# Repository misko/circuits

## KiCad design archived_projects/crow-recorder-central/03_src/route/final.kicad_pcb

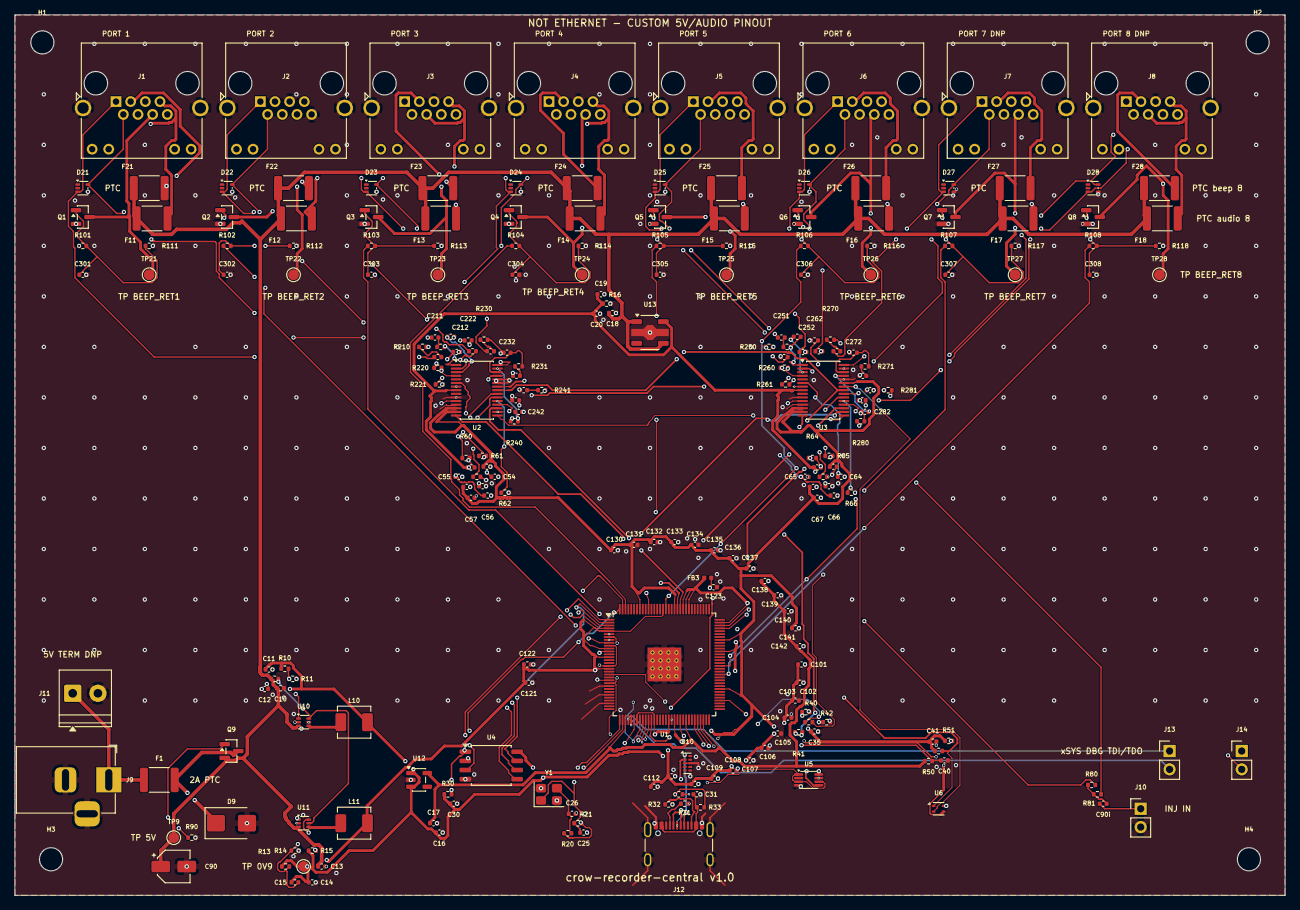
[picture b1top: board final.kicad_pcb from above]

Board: 6 copper layers, 176.0 x 122.0 mm, 238 parts (0 on the bottom side), 151 nets.

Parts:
C10, C13, C18: 4u7 VIN; C_0402_1005Metric
C11, C136, C137: 10u 3V3; C_0402_1005Metric
C12: 100p FF; C_0402_1005Metric
C14: 22u 0V9; C_0402_1005Metric
C15: 560p FF; C_0402_1005Metric
C16: 1u VIN; C_0402_1005Metric
C17: 1u 1V8; C_0402_1005Metric
C19: 10u 3V3A; C_0402_1005Metric
C20: 100n 3V3A; C_0402_1005Metric
C25: 18p CL1; C_0402_1005Metric
C26: 18p CL2; C_0402_1005Metric
C30: 100n flash; C_0402_1005Metric
C31: 1u VBUS; C_0402_1005Metric
C35: 100n buf; C_0402_1005Metric
C40: 10n RST; C_0402_1005Metric
C41: 100n SHT; C_0402_1005Metric
C50: 4u7 AVDD_A; C_0402_1005Metric
C51: 100n AVDD_A; C_0402_1005Metric
C52: 4u7 DVDD_A; C_0402_1005Metric
C53: 100n DVDD_A; C_0402_1005Metric
C54: 2u2 VREF_A; C_0402_1005Metric
C55: 2u2 LDO_A; C_0402_1005Metric
C56: 100n LDO_A; C_0402_1005Metric
C57: 100n IOV_A; C_0402_1005Metric
C60: 4u7 AVDD_B; C_0402_1005Metric
C61: 100n AVDD_B; C_0402_1005Metric
C62: 4u7 DVDD_B; C_0402_1005Metric
C63: 100n DVDD_B; C_0402_1005Metric
C64: 2u2 VREF_B; C_0402_1005Metric
C65: 2u2 LDO_B; C_0402_1005Metric
C66: 100n LDO_B; C_0402_1005Metric
C67: 100n IOV_B; C_0402_1005Metric
C90: 100u 5V bulk; CP_Elec_4x5.4
C90i: 1u inj; C_0402_1005Metric
C101, C102, C103, C104, C105, C106, C107, C108, C109, C110, C111, C112: 100n VDD; C_0402_1005Metric
C121, C122: 10u VDD; C_0402_1005Metric
C123: 1u PLL; C_0402_1005Metric
C130, C131, C132, C133, C134, C135: 100n 3V3; C_0402_1005Metric
C138, C139: 100n 1V8; C_0402_1005Metric
C140: 10u 1V8; C_0402_1005Metric
C141: 100n USB33; C_0402_1005Metric
C142: 100n USB18; C_0402_1005Metric
C210: 1u cpl P1; C_0402_1005Metric
C211: 1u cpl N1; C_0402_1005Metric
C212: 1n diff 1; C_0402_1005Metric
C220: 1u cpl P2; C_0402_1005Metric
C221: 1u cpl N2; C_0402_1005Metric
C222: 1n diff 2; C_0402_1005Metric
C230: 1u cpl P3; C_0402_1005Metric
C231: 1u cpl N3; C_0402_1005Metric
C232: 1n diff 3; C_0402_1005Metric
C240: 1u cpl P4; C_0402_1005Metric
C241: 1u cpl N4; C_0402_1005Metric
C242: 1n diff 4; C_0402_1005Metric
C250: 1u cpl P5; C_0402_1005Metric
C251: 1u cpl N5; C_0402_1005Metric
C252: 1n diff 5; C_0402_1005Metric
C260: 1u cpl P6; C_0402_1005Metric
C261: 1u cpl N6; C_0402_1005Metric
C262: 1n diff 6; C_0402_1005Metric
C270: 1u cpl P7; C_0402_1005Metric
C271: 1u cpl N7; C_0402_1005Metric
C272: 1n diff 7; C_0402_1005Metric
C280: 1u cpl P8; C_0402_1005Metric
C281: 1u cpl N8; C_0402_1005Metric
C282: 1n diff 8; C_0402_1005Metric
C301: 4n7 gate 1; C_0402_1005Metric
C302: 4n7 gate 2; C_0402_1005Metric
C303: 4n7 gate 3; C_0402_1005Metric
C304: 4n7 gate 4; C_0402_1005Metric
C305: 4n7 gate 5; C_0402_1005Metric
C306: 4n7 gate 6; C_0402_1005Metric
C307: 4n7 gate 7; C_0402_1005Metric
C308: 4n7 gate 8; C_0402_1005Metric
D9: SMBJ5.0A TVS; D_SMB
D10: TPD4EUSB30; USON-10_2.5x1.0mm_P0.5mm
D21: TPD2E2U06 p1; SOT-553
D22: TPD2E2U06 p2; SOT-553
D23: TPD2E2U06 p3; SOT-553
D24: TPD2E2U06 p4; SOT-553
D25: TPD2E2U06 p5; SOT-553
D26: TPD2E2U06 p6; SOT-553
D27: TPD2E2U06 p7; SOT-553
D28: TPD2E2U06 p8; SOT-553
F1: 2A PTC; Fuse_1812_4532Metric
F11: PTC audio 1; Fuse_1812_4532Metric
F12: PTC audio 2; Fuse_1812_4532Metric
F13: PTC audio 3; Fuse_1812_4532Metric
F14: PTC audio 4; Fuse_1812_4532Metric
F15: PTC audio 5; Fuse_1812_4532Metric
F16: PTC audio 6; Fuse_1812_4532Metric
F17: PTC audio 7; Fuse_1812_4532Metric
F18: PTC audio 8; Fuse_1812_4532Metric
F21: PTC beep 1; Fuse_1812_4532Metric
F22: PTC beep 2; Fuse_1812_4532Metric
F23: PTC beep 3; Fuse_1812_4532Metric
F24: PTC beep 4; Fuse_1812_4532Metric
F25: PTC beep 5; Fuse_1812_4532Metric
F26: PTC beep 6; Fuse_1812_4532Metric
F27: PTC beep 7; Fuse_1812_4532Metric
F28: PTC beep 8; Fuse_1812_4532Metric
FB3: 600R PLL; L_0402_1005Metric
H1, H2, H3, H4: MountingHole_3.2mm_M3
J1, J2, J3, J4, J5, J6: RJHSE-5384; RJ45_Amphenol_RJHSE538X
J7, J8: RJHSE-5384 DNP; RJ45_Amphenol_RJHSE538X
J9: DC-005 5V IN; BarrelJack_Horizontal
J10: INJ IN; PinHeader_1x02_P2.54mm_Vertical
J11: 5V TERM DNP; TerminalBlock_Phoenix_PT-1,5-2-3.5-H_1x02_P3.50mm_Horizontal
J12: USB4105-GF-A; USB_C_Receptacle_GCT_USB4105-xx-A_16P_TopMnt_Horizontal
J13: xSYS DBG TDI/TDO; PinHeader_1x02_P2.54mm_Vertical
J14: xSYS DBG TMS/TCK; PinHeader_1x02_P2.54mm_Vertical
L10: 1u0 3V3; L_Sunlord_MWSA0402S
L11: 1u0 0V9; L_Sunlord_MWSA0402S
Q1: AO3400A beep 1; SOT-23
Q2: AO3400A beep 2; SOT-23
Q3: AO3400A beep 3; SOT-23
Q4: AO3400A beep 4; SOT-23
Q5: AO3400A beep 5; SOT-23
Q6: AO3400A beep 6; SOT-23
Q7: AO3400A beep 7; SOT-23
Q8: AO3400A beep 8; SOT-23
Q9: AO3401A revFET; SOT-23
R10: 68k FB1 hi; R_0402_1005Metric
R11: 15k FB1 lo; R_0402_1005Metric
R12: 10k PG1 pu; R_0402_1005Metric
R13: 10k FB2 hi; R_0402_1005Metric
R14: 20k FB2 lo; R_0402_1005Metric
R15: 10k PG2 pu; R_0402_1005Metric
R16: 4k7 bleed; R_0402_1005Metric
R20: 680R Rd; R_0402_1005Metric
R21: 1M Rf; R_0402_1005Metric
R30: 10k CS pu; R_0402_1005Metric
R31: 5k1 CC1 Rd; R_0402_1005Metric
R32: 5k1 CC2 Rd; R_0402_1005Metric
R33: 220k VBUS; R_0402_1005Metric
R34: 330k VBUS; R_0402_1005Metric
R40: 33R MCLK_A; R_0402_1005Metric
R41: 33R MCLK_B; R_0402_1005Metric
R42: 33R BCLK; R_0402_1005Metric
R43: 33R LRCK; R_0402_1005Metric
R50: 10k RST pu; R_0402_1005Metric
R51: 4k7 SCL pu; R_0402_1005Metric
R52: 4k7 SDA pu; R_0402_1005Metric
R60: 100k GP0_A; R_0402_1005Metric
R61: 100k GP1_A; R_0402_1005Metric
R62: 100k GP2_A; R_0402_1005Metric
R63: 100k GP3_A; R_0402_1005Metric
R64: 100k GP0_B; R_0402_1005Metric
R65: 100k GP1_B; R_0402_1005Metric
R66: 100k GP2_B; R_0402_1005Metric
R67: 100k GP3_B; R_0402_1005Metric
R80: 1k inj ch4; R_0402_1005Metric
R81: 1k inj ch8; R_0402_1005Metric
R90: 100k FET gate; R_0402_1005Metric
R101: 1k gate 1; R_0402_1005Metric
R102: 1k gate 2; R_0402_1005Metric
R103: 1k gate 3; R_0402_1005Metric
R104: 1k gate 4; R_0402_1005Metric
R105: 1k gate 5; R_0402_1005Metric
R106: 1k gate 6; R_0402_1005Metric
R107: 1k gate 7; R_0402_1005Metric
R108: 1k gate 8; R_0402_1005Metric
R111: 100k pd 1; R_0402_1005Metric
R112: 100k pd 2; R_0402_1005Metric
R113: 100k pd 3; R_0402_1005Metric
R114: 100k pd 4; R_0402_1005Metric
R115: 100k pd 5; R_0402_1005Metric
R116: 100k pd 6; R_0402_1005Metric
R117: 100k pd 7; R_0402_1005Metric
R118: 100k pd 8; R_0402_1005Metric
R210: 49R9 P1; R_0402_1005Metric
R211: 49R9 N1; R_0402_1005Metric
R220: 49R9 P2; R_0402_1005Metric
R221: 49R9 N2; R_0402_1005Metric
R230: 49R9 P3; R_0402_1005Metric
R231: 49R9 N3; R_0402_1005Metric
R240: 49R9 P4; R_0402_1005Metric
R241: 49R9 N4; R_0402_1005Metric
R250: 49R9 P5; R_0402_1005Metric
R251: 49R9 N5; R_0402_1005Metric
R260: 49R9 P6; R_0402_1005Metric
R261: 49R9 N6; R_0402_1005Metric
R270: 49R9 P7; R_0402_1005Metric
R271: 49R9 N7; R_0402_1005Metric
R280: 49R9 P8; R_0402_1005Metric
R281: 49R9 N8; R_0402_1005Metric
TP9: TP 5V; TestPoint_Pad_D1.5mm
TP11: TP 0V9; TestPoint_Pad_D1.5mm
TP21: TP BEEP_RET1; TestPoint_Pad_D1.5mm
TP22: TP BEEP_RET2; TestPoint_Pad_D1.5mm
TP23: TP BEEP_RET3; TestPoint_Pad_D1.5mm
TP24: TP BEEP_RET4; TestPoint_Pad_D1.5mm
TP25: TP BEEP_RET5; TestPoint_Pad_D1.5mm
TP26: TP BEEP_RET6; TestPoint_Pad_D1.5mm
TP27: TP BEEP_RET7; TestPoint_Pad_D1.5mm
TP28: TP BEEP_RET8; TestPoint_Pad_D1.5mm
U1: XU316-1024-TQ128-I24; TQFP-128_14x14mm_P0.4mm_EP4.7mm
U2, U3: PCM1865DBTR; TSSOP-30_4.4x7.8mm_P0.5mm
U4: W25Q16JVSSIQ; SOIC-8_5.3x5.3mm_P1.27mm
U5: NC7NZ34 MCLK buf; VSSOP-8_2.3x2mm_P0.5mm
U6: SHT40-AD1B (0x44); Sensirion_DFN-4_1.5x1.5mm_P0.8mm_SHT4x_NoCentralPad
U10: AP61102 3V3; SOT-563
U11: AP61102 0V9; SOT-563
U12: TCR2LF18 1V8; SOT-23-5
U13: XC6227 3V3A; SOT-89-5
Y1: FA-238 24MHz; Crystal_SMD_3225-4Pin_3.2x2.5mm

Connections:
0V9: C14.1, C15.1, C101.1, C102.1, C103.1, C104.1, C105.1, C106.1, C107.1, C108.1, C109.1, C110.1, C111.1, C112.1, C121.1, C122.1, FB3.1, L11.2, R13.1, TP11.1, U1.5, U1.11, U1.14, U1.18, U1.39, U1.45, U1.50, U1.54, U1.68, U1.85, U1.95, U1.104, U1.105, U1.106, U1.113
1V8: C17.1, C138.1, C139.1, C140.1, C142.1, R50.1, U1.35, U1.56, U1.62, U12.5
3V3: C11.1, C12.1, C16.1, C30.1, C35.1, C41.1, C52.1, C53.1, C57.1, C62.1, C63.1, C67.1, C130.1, C131.1, C132.1, C133.1, C134.1, C135.1, C136.1, C137.1, C141.1, L10.2, R10.1, R15.1, R30.1, R51.1, R52.1, U1.10, U1.17, U1.40, U1.43, U1.52, U1.61, U1.72, U1.89, U1.109, U1.121, U2.13, U2.14, U3.13, U3.14, U3.25, U4.8, U5.8, U6.3, U12.1, U12.3
3V3A: C19.1, C20.1, C50.1, C51.1, C60.1, C61.1, R16.1, U2.8, U3.8, U13.5
5V: C10.1, C13.1, C18.1, C90.1, F11.1, F12.1, F13.1, F14.1, F15.1, F16.1, F17.1, F18.1, F21.1, F22.1, F23.1, F24.1, F25.1, F26.1, F27.1, F28.1, Q9.2, R12.1, TP9.1, U10.3, U10.5, U11.3, U13.1, U13.4
5V_AUD1: F11.2, J1.4, J1.7
5V_AUD2: F12.2, J2.4, J2.7
5V_AUD3: F13.2, J3.4, J3.7
5V_AUD4: F14.2, J4.4, J4.7
5V_AUD5: F15.2, J5.4, J5.7
5V_AUD6: F16.2, J6.4, J6.7
5V_AUD7: F17.2, J7.4, J7.7
5V_AUD8: F18.2, J8.4, J8.7
5V_IN: F1.1, J9.1, J11.1
5V_P: D9.1, F1.2, Q9.3
AIN_N1: C211.2, R211.1
AIN_N2: C221.2, R221.1
AIN_N3: C231.2, R231.1
AIN_N4: C241.2, R241.1
AIN_N5: C251.2, R251.1
AIN_N6: C261.2, R261.1
AIN_N7: C271.2, R271.1
AIN_N8: C281.2, R281.1
AIN_P1: C210.2, R210.1
AIN_P2: C220.2, R220.1
AIN_P3: C230.2, R230.1
AIN_P4: C240.2, R80.2, R240.1
AIN_P5: C250.2, R250.1
AIN_P6: C260.2, R260.1
AIN_P7: C270.2, R270.1
AIN_P8: C280.2, R81.2, R280.1
AUD_N1: C211.1, D21.5, J1.2
AUD_N2: C221.1, D22.5, J2.2
AUD_N3: C231.1, D23.5, J3.2
AUD_N4: C241.1, D24.5, J4.2
AUD_N5: C251.1, D25.5, J5.2
AUD_N6: C261.1, D26.5, J6.2
AUD_N7: C271.1, D27.5, J7.2
AUD_N8: C281.1, D28.5, J8.2
AUD_P1: C210.1, D21.3, J1.1
AUD_P2: C220.1, D22.3, J2.1
AUD_P3: C230.1, D23.3, J3.1
AUD_P4: C240.1, D24.3, J4.1
AUD_P5: C250.1, D25.3, J5.1
AUD_P6: C260.1, D26.3, J6.1
AUD_P7: C270.1, D27.3, J7.1
AUD_P8: C280.1, D28.3, J8.1
BCLK: R42.2, U2.17, U3.17
BCLK_X: R42.1, U1.22
BEEP_5V1: F21.2, J1.3
BEEP_5V2: F22.2, J2.3
BEEP_5V3: F23.2, J3.3
BEEP_5V4: F24.2, J4.3
BEEP_5V5: F25.2, J5.3
BEEP_5V6: F26.2, J6.3
BEEP_5V7: F27.2, J7.3
BEEP_5V8: F28.2, J8.3
BEEP_G1: R101.1, U1.6
BEEP_G2: R102.1, U1.9
BEEP_G3: R103.1, U1.12
BEEP_G4: R104.1, U1.126
BEEP_G5: R105.1, U1.118
BEEP_G6: R106.1, U1.112
BEEP_G7: R107.1, U1.80
BEEP_G8: R108.1, U1.77
BEEP_RET1: J1.6, Q1.3, TP21.1
BEEP_RET2: J2.6, Q2.3, TP22.1
BEEP_RET3: J3.6, Q3.3, TP23.1
BEEP_RET4: J4.6, Q4.3, TP24.1
BEEP_RET5: J5.6, Q5.3, TP25.1
BEEP_RET6: J6.6, Q6.3, TP26.1
BEEP_RET7: J7.6, Q7.3, TP27.1
BEEP_RET8: J8.6, Q8.3, TP28.1
BG_1: C301.1, Q1.1, R101.2, R111.1
BG_2: C302.1, Q2.1, R102.2, R112.1
BG_3: C303.1, Q3.1, R103.2, R113.1
BG_4: C304.1, Q4.1, R104.2, R114.1
BG_5: C305.1, Q5.1, R105.2, R115.1
BG_6: C306.1, Q6.1, R106.2, R116.1
BG_7: C307.1, Q7.1, R107.2, R117.1
BG_8: C308.1, Q8.1, R108.2, R118.1
BK1_PG: R12.2, U10.6, U11.5
BK1_SW: L10.1, U10.4
BK2_PG: R15.2, U11.6
BK2_SW: L11.1, U11.4
CC1: J12.A5, R31.1
CC2: J12.B5, R32.1
DATA1: U1.107, U2.18
DATA2: U1.108, U3.18
FB1: C12.2, R10.2, R11.1, U10.1
FB2: C15.2, R13.2, R14.1, U11.1
GATE9: Q9.1, R90.1
GND: C10.2, C11.2, C13.2, C14.2, C16.2, C17.2, C18.2, C19.2, C20.2, C25.2, C26.2, C30.2, C31.2, C35.2, C40.2, C41.2, C50.2, C51.2, C52.2, C53.2, C54.2, C55.2, C56.2, C57.2, C60.2, C61.2, C62.2, C63.2, C64.2, C65.2, C66.2, C67.2, C90.2, C101.2, C102.2, C103.2, C104.2, C105.2, C106.2, C107.2, C108.2, C109.2, C110.2, C111.2, C112.2, C121.2, C122.2, C123.2, C130.2, C131.2, C132.2, C133.2, C134.2, C135.2, C136.2, C137.2, C138.2, C139.2, C140.2, C141.2, C142.2, C301.2, C302.2, C303.2, C304.2, C305.2, C306.2, C307.2, C308.2, D9.2, D10.3, D10.8, D21.4, D22.4, D23.4, D24.4, D25.4, D26.4, D27.4, D28.4, J1.5, J1.8, J1.SH, J2.5, J2.8, J2.SH, J3.5, J3.8, J3.SH, J4.5, J4.8, J4.SH, J5.5, J5.8, J5.SH, J6.5, J6.8, J6.SH, J7.5, J7.8, J7.SH, J8.5, J8.8, J8.SH, J9.2, J9.3, J10.2, J11.2, J12.A1, J12.A12, J12.B1, J12.B12, J12.SH, Q1.2, Q2.2, Q3.2, Q4.2, Q5.2, Q6.2, Q7.2, Q8.2, R11.2, R14.2, R16.2, R31.2, R32.2, R34.2, R60.2, R61.2, R62.2, R63.2, R64.2, R65.2, R66.2, R67.2, R90.2, R111.2, R112.2, R113.2, R114.2, R115.2, R116.2, R117.2, R118.2, U1.24, U1.27, U1.30, U1.42, U1.129, U2.7, U2.10, U2.12, U2.25, U2.26, U3.7, U3.10, U3.12, U3.26, U4.4, U5.4, U6.4, U10.2, U11.2, U12.2, U13.2, Y1.2, Y1.4
GP0_A: R60.1, U2.22
GP0_B: R64.1, U3.22
GP1_A: R61.1, U2.21
GP1_B: R65.1, U3.21
GP2_A: R62.1, U2.20
GP2_B: R66.1, U3.20
GP3_A: R63.1, U2.19
GP3_B: R67.1, U3.19
I2C_SCL: R51.2, U1.93, U2.24, U3.24, U6.2
I2C_SDA: R52.2, U1.94, U2.23, U3.23, U6.1
INJ: C90i.1, J10.1
INJ_C: C90i.2, R80.1, R81.1
LDO_A: C55.1, C56.1, U2.11
LDO_B: C65.1, C66.1, U3.11
LRCK: R43.2, U2.16, U3.16
LRCK_X: R43.1, U1.20
MCLK_A: R40.2, U2.15
MCLK_A0: R40.1, U5.7
MCLK_B: R41.2, U3.15
MCLK_B0: R41.1, U5.5
MCLK_SRC: U1.7, U1.23, U5.1, U5.3, U5.6
PLL_AVDD: C123.1, FB3.2, U1.41
QSPI_CLK: U1.4, U4.6
QSPI_CS: R30.2, U1.2, U4.1
QSPI_D0: U1.127, U4.5
QSPI_D1: U1.128, U4.2
QSPI_D2: U1.1, U4.3
QSPI_D3: U1.3, U4.7
RST_N: C40.1, R50.2, U1.38
TCK: J14.2, U1.51
TDI: J13.1, U1.36
TDO: J13.2, U1.37
TMS: J14.1, U1.44
USB_DM: D10.2, J12.A7, J12.B7, U1.59
USB_DP: D10.1, J12.A6, J12.B6, U1.60
VA1M: C212.2, R211.2, U2.1
VA1P: C212.1, R210.2, U2.3
VA2M: C222.2, R221.2, U2.2
VA2P: C222.1, R220.2, U2.4
VA3M: C232.2, R231.2, U2.28
VA3P: C232.1, R230.2, U2.30
VA4M: C242.2, R241.2, U2.27
VA4P: C242.1, R240.2, U2.29
VB1M: C252.2, R251.2, U3.1
VB1P: C252.1, R250.2, U3.3
VB2M: C262.2, R261.2, U3.2
VB2P: C262.1, R260.2, U3.4
VB3M: C272.2, R271.2, U3.28
VB3P: C272.1, R270.2, U3.30
VB4M: C282.2, R281.2, U3.27
VB4P: C282.1, R280.2, U3.29
VBUS: C31.1, J12.A4, J12.A9, J12.B4, J12.B9, R33.1
VBUS_DET: R33.2, R34.1, U1.8
VREF_A: C54.1, U2.6
VREF_B: C64.1, U3.6
XIN: C25.1, R21.1, U1.34, Y1.1
XOUT: R20.1, R21.2, U1.33
XTAL2: C26.1, R20.2, Y1.3

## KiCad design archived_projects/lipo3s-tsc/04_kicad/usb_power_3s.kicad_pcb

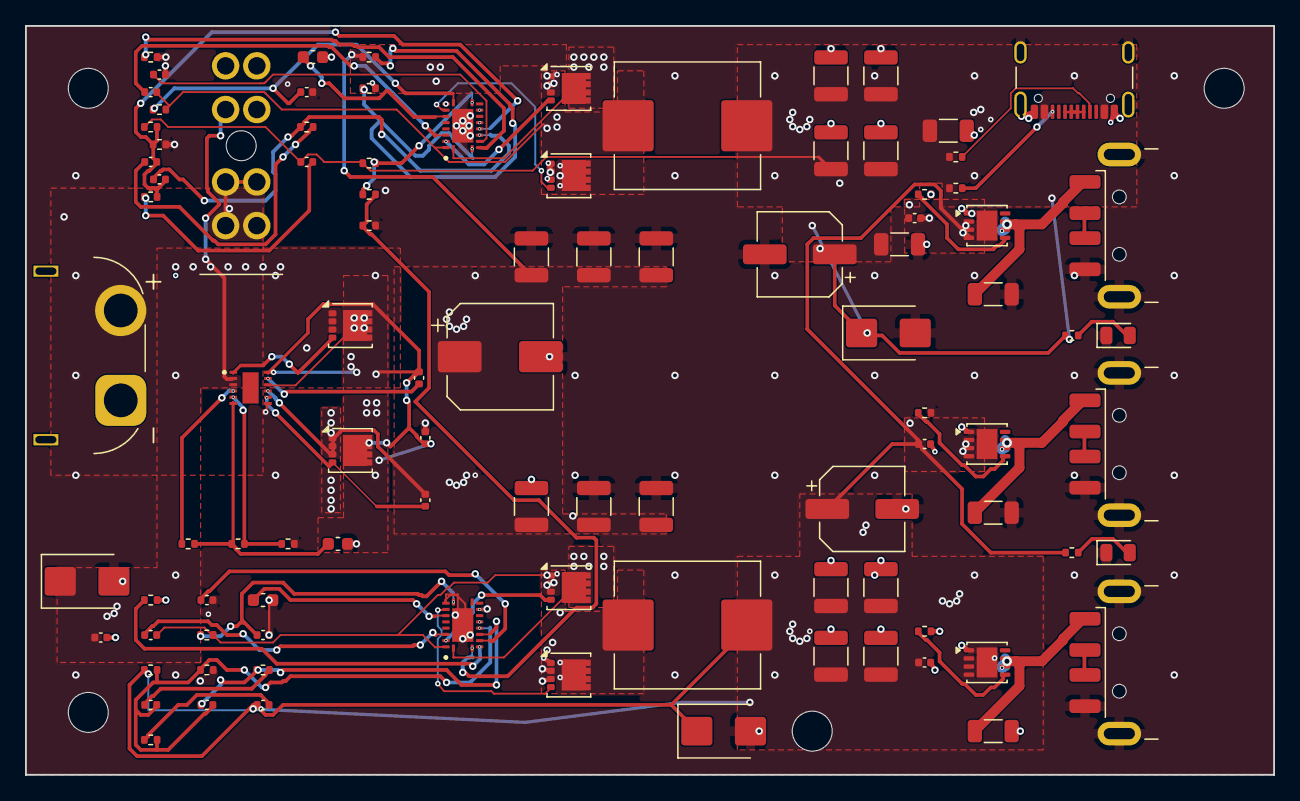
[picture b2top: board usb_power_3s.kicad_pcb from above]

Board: 4 copper layers, 100.0 x 60.0 mm, 100 parts (0 on the bottom side), 54 nets.

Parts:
C1, C2, C15, C20, C21, C22: 100nF; C_0402_1005Metric
C3: 47nF; C_0402_1005Metric
C16: 2.2uF; C_0603_1608Metric
C30, C31, C32, C33, C34: 22uF; C_1206_3216Metric
CA1: 47nF; C_0402_1005Metric
CA2: 2.2uF; C_0603_1608Metric
CA3: 100nF; C_0402_1005Metric
CA4: 18pF; C_0402_1005Metric
CA7: 220uF; CP_Elec_6.3x5.9
CA8: 8.2nF; C_0402_1005Metric
CA9: 39pF; C_0402_1005Metric
CA10: 1.2nF; C_0402_1005Metric
CA51, CA52, CA53: 10uF; C_1210_3225Metric
CA61, CA62, CA63, CA64: 47uF; C_1210_3225Metric
CB1: 47nF; C_0402_1005Metric
CB2: 2.2uF; C_0603_1608Metric
CB3: 100nF; C_0402_1005Metric
CB4: 18pF; C_0402_1005Metric
CB7: 220uF; CP_Elec_6.3x5.9
CB8: 8.2nF; C_0402_1005Metric
CB9: 39pF; C_0402_1005Metric
CB10: 1.2nF; C_0402_1005Metric
CB51, CB52, CB53: 10uF; C_1210_3225Metric
CB61, CB62, CB63, CB64: 47uF; C_1210_3225Metric
CE1: 100uF; CP_Elec_8x10
D1: C353386; D_SMB
D2, D3: C113974; D_SMB
D4, D5: C2297; LED_0805_2012Metric
F1: C207061; FuseHolder_ATO_FLR_EdgeTrim
H1, H2, H3, H4: MountingHole_3.2mm_M3
J1: C98732; XT60PW-M_EdgeTrim
J2, J3, J4: 1001-011-01101; USB_A_CNCTech_1001-011-01101_Horizontal
J5: C3020560; USB_C_Receptacle_GCT_USB4105-xx-A_16P_TopMnt_Horizontal
LA1: C17700181; L_Sunlord_MWSA1005S
LB1: C17700181; L_Sunlord_MWSA1005S
Q1, Q2: C840100; VSON-8_3.3x3.3mm_P0.65mm_NexFET
QA1, QA2: C840100; VSON-8_3.3x3.3mm_P0.65mm_NexFET
QB1, QB2: C840100; VSON-8_3.3x3.3mm_P0.65mm_NexFET
R1: 887kΩ; R_0402_1005Metric
R2: 52.3kΩ; R_0402_1005Metric
R3: 82.5kΩ; R_0402_1005Metric
R4: 100kΩ; R_0402_1005Metric
R5, R34: 16.5kΩ; R_0402_1005Metric
R16, R17, R18: 24.3kΩ; R_0402_1005Metric
R19, R20: 10kΩ; R_0402_1005Metric
R21, R33: 20kΩ; R_0402_1005Metric
R22, R23: 1kΩ; R_0402_1005Metric
RA1: 16.5kΩ; R_0402_1005Metric
RA2: 348Ω; R_0402_1005Metric
RA3: 20kΩ; R_0402_1005Metric
RA4: 3.74kΩ; R_0402_1005Metric
RA5: 13kΩ; R_0402_1005Metric
RA6: 4.64kΩ; R_0402_1005Metric
RB1: 16.5kΩ; R_0402_1005Metric
RB2: 432Ω; R_0402_1005Metric
RB3: 20kΩ; R_0402_1005Metric
RB4: 3.74kΩ; R_0402_1005Metric
RB5: 13kΩ; R_0402_1005Metric
RB6: 4.64kΩ; R_0402_1005Metric
U1: C3215600; WSON-12_3x3_P0.5_LM74800DRR
U2, U3: C485912; VQFN-20_3.5x4.5_P0.5_LM5145RGY
U4, U5, U6: C130056; VSON-8-1EP_3x3mm_P0.65mm_EP1.65x2.4mm

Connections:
5V_A: C20.1, C21.1, C22.1, CB7.1, CB10.1, CB61.1, CB62.1, CB63.1, CB64.1, D2.1, LB1.2, R22.1, RB3.1, U4.2, U4.3, U4.4, U5.2, U5.3, U5.4, U6.2, U6.3, U6.4
5V_C: C33.1, C34.1, CA7.1, CA10.1, CA61.1, CA62.1, CA63.1, CA64.1, D3.1, J5.A4, J5.A9, J5.B4, J5.B9, LA1.2, R19.1, R20.1, R21.1, R23.1, RA3.1
BST_A: CA3.1, U2.17
BST_B: CB3.1, U3.17
CC1: J5.A5, R19.2
CC2: J5.B5, R20.2
COMP_A: CA9.1, RA5.1, U2.4
COMP_B: CB9.1, RB5.1, U3.4
CX_A: CA8.1, RA5.2
CX_B: CB8.1, RB5.2
CY_A: CA10.2, RA6.1
CY_B: CB10.2, RB6.1
DCP1: J2.2, J2.3
DCP2: J3.2, J3.3
DCP3: J4.2, J4.3
DCPC: J5.A6, J5.A7, J5.B6, J5.B7
DG_FE: Q1.4, U1.1
EN_A: R4.2, R5.1, U2.1
FB_A: CA8.2, CA9.2, RA3.2, RA4.1, RA6.2, U2.5
FB_B: CB8.2, CB9.2, RB3.2, RB4.1, RB6.2, U3.5
FE_CAP: C1.1, U1.11
FE_EN: C16.1, R1.2, R2.1, U1.6
FE_LAD: R1.1, U1.4
FE_MID: C1.2, C2.1, Q1.5, Q2.5, U1.10, U1.12
FE_OV: R2.2, R3.1, U1.5
GND: C2.2, C15.2, C16.2, C20.2, C21.2, C22.2, C30.2, C31.2, C32.2, C33.2, C34.2, CA1.2, CA2.2, CA4.2, CA7.2, CA51.2, CA52.2, CA53.2, CA61.2, CA62.2, CA63.2, CA64.2, CB1.2, CB2.2, CB4.2, CB7.2, CB51.2, CB52.2, CB53.2, CB61.2, CB62.2, CB63.2, CB64.2, CE1.2, D1.2, D2.2, D3.2, D4.1, D5.1, J1.1, J2.4, J2.SH, J3.4, J3.SH, J4.4, J4.SH, J5.A1, J5.A12, J5.B1, J5.B12, J5.SH, QA2.1, QA2.2, QA2.3, QB2.1, QB2.2, QB2.3, R3.2, R5.2, R16.2, R17.2, R18.2, R34.2, RA1.2, RA4.2, RB1.2, RB4.2, U1.7, U2.6, U2.8, U2.12, U2.21, U3.6, U3.8, U3.12, U3.21, U4.1, U4.9, U5.1, U5.9, U6.1, U6.9
HG_FE: C3.1, Q2.4, U1.8
HO_A: QA1.4, U2.18
HO_B: QB1.4, U3.18
ILIM1: R16.1, U4.5
ILIM2: R17.1, U5.5
ILIM3: R18.1, U6.5
ILIM_A: CA4.1, RA2.1, U2.11
ILIM_B: CB4.1, RB2.1, U3.11
LEDA_A: D4.2, R22.2
LEDC_A: D5.2, R23.2
LO_A: QA2.4, U2.13
LO_B: QB2.4, U3.13
PGOODA_RAW: R21.2, R33.1, U2.10
PGOOD_A: R33.2, R34.1, U3.1
RT_A: RA1.1, U2.2
RT_B: RB1.1, U3.2
SS_A: CA1.1, U2.3
SS_B: CB1.1, U3.3
SW_A: CA3.2, LA1.1, QA1.1, QA1.2, QA1.3, QA2.5, RA2.2, U2.19
SW_B: CB3.2, LB1.1, QB1.1, QB1.2, QB1.3, QB2.5, RB2.2, U3.19
VBATT_F: C15.1, D1.1, F1.2, Q1.1, Q1.2, Q1.3, U1.2, U1.3
VBATT_RAW: F1.1, J1.2
VBUS1: C30.1, J2.1, U4.6, U4.7
VBUS2: C31.1, J3.1, U5.6, U5.7
VBUS3: C32.1, J4.1, U6.6, U6.7
VCC_A: CA2.1, U2.14
VCC_B: CB2.1, U3.14
VSW: C3.2, CA51.1, CA52.1, CA53.1, CB51.1, CB52.1, CB53.1, CE1.1, Q2.1, Q2.2, Q2.3, QA1.5, QB1.5, R4.1, U1.9, U2.20, U3.20

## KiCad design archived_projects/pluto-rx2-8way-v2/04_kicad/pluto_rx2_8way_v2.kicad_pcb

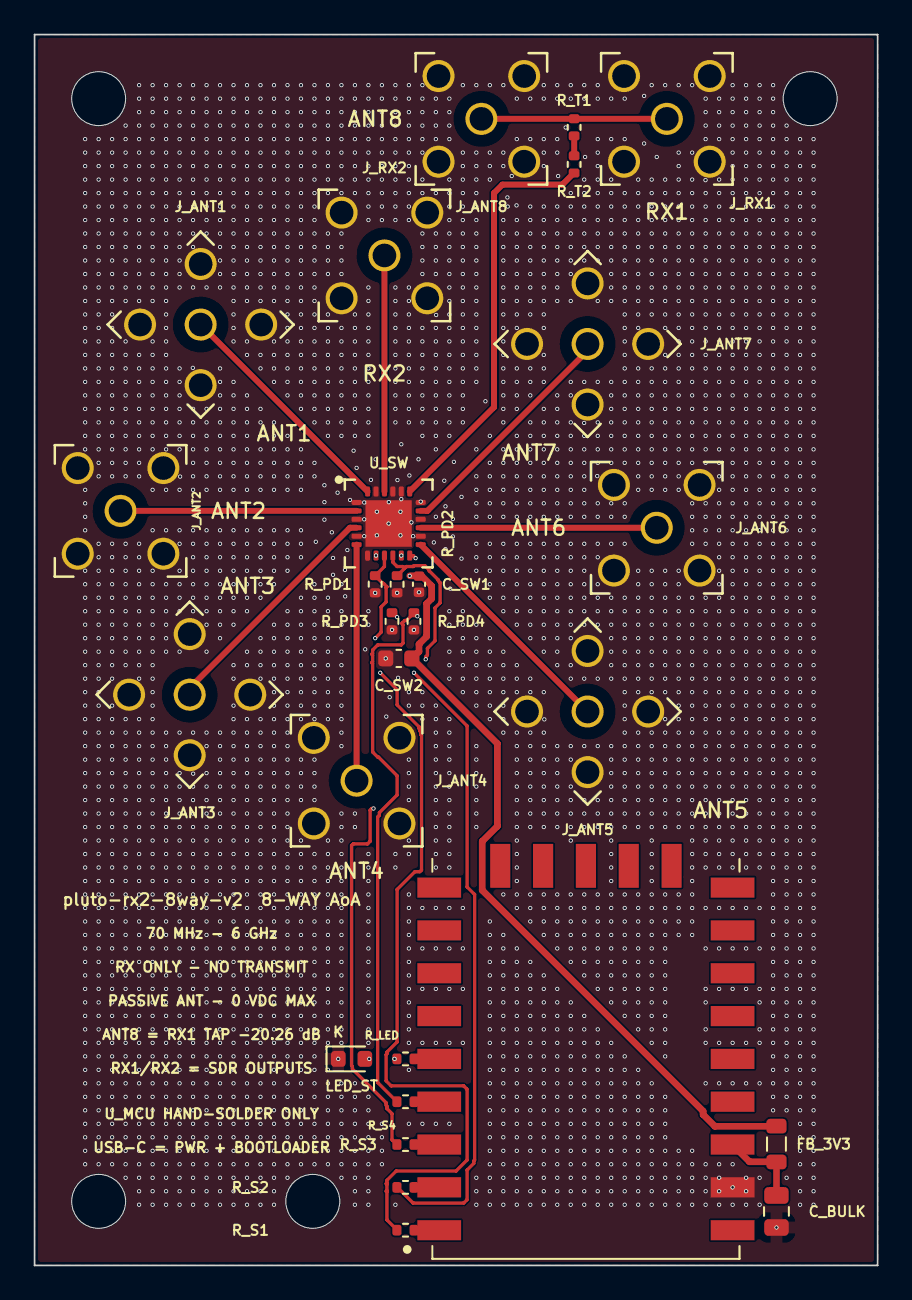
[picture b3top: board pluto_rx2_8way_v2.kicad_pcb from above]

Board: 4 copper layers, 50.0 x 73.0 mm, 32 parts (0 on the bottom side), 24 nets.

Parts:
C_BULK: 4.7uF; C_0805_2012Metric
C_SW1: 100nF; C_0402_1005Metric
C_SW2: 1uF; C_0603_1608Metric
FB_3V3: C3716677; L_0805_2012Metric
H1, H2, H3, H4: MountingHole_3.2mm_M3
J_ANT1, J_ANT2, J_ANT3, J_ANT4, J_ANT5, J_ANT6, J_ANT7, J_ANT8: C504007; SMA_Vertical_5.08sq_D1.4
J_RX1, J_RX2: C504007; SMA_Vertical_5.08sq_D1.4
LED_ST: C2286; LED_0603_1608Metric
R_LED: 680Ω; R_0402_1005Metric
R_PD1, R_PD2, R_PD3, R_PD4: 10kΩ; R_0402_1005Metric
R_S1, R_S2, R_S3, R_S4: 47Ω; R_0402_1005Metric
R_T1, R_T2: 220Ω; R_0402_1005Metric
U_MCU: C9900173620; RP2040_Zero_LCC23_18x23.5
U_SW: C5121458; QFN-24_4x4_P0.5_EP2.7_PE42482

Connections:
3V3: C_SW1.1, C_SW2.1, FB_3V3.2, U_SW.8
3V3_MOD: C_BULK.1, FB_3V3.1, U_MCU.21
ANT1: J_ANT1.1, U_SW.24
ANT2: J_ANT2.1, U_SW.2
ANT3: J_ANT3.1, U_SW.4
ANT4: J_ANT4.1, U_SW.6
ANT5: J_ANT5.1, U_SW.13
ANT6: J_ANT6.1, U_SW.15
ANT7: J_ANT7.1, U_SW.17
GND: C_BULK.2, C_SW1.2, C_SW2.2, J_ANT1.2, J_ANT1.3, J_ANT1.4, J_ANT1.5, J_ANT2.2, J_ANT2.3, J_ANT2.4, J_ANT2.5, J_ANT3.2, J_ANT3.3, J_ANT3.4, J_ANT3.5, J_ANT4.2, J_ANT4.3, J_ANT4.4, J_ANT4.5, J_ANT5.2, J_ANT5.3, J_ANT5.4, J_ANT5.5, J_ANT6.2, J_ANT6.3, J_ANT6.4, J_ANT6.5, J_ANT7.2, J_ANT7.3, J_ANT7.4, J_ANT7.5, J_ANT8.2, J_ANT8.3, J_ANT8.4, J_ANT8.5, J_RX1.2, J_RX1.3, J_RX1.4, J_RX1.5, J_RX2.2, J_RX2.3, J_RX2.4, J_RX2.5, LED_ST.1, R_PD1.2, R_PD2.2, R_PD3.2, R_PD4.2, U_MCU.22, U_SW.1, U_SW.3, U_SW.5, U_SW.7, U_SW.14, U_SW.16, U_SW.18, U_SW.20, U_SW.21, U_SW.23, U_SW.25
LED_STAT: R_LED.1, U_MCU.5
LED_STAT_A: LED_ST.2, R_LED.2
RX1_MAIN: J_ANT8.1, J_RX1.1, R_T1.1
RX1_TAP: R_T2.2, U_SW.19
RX1_TAP_MID: R_T1.2, R_T2.1
RX2_OUT: J_RX2.1, U_SW.22
SEL_V1: R_S1.1, U_MCU.1
SEL_V2: R_S2.1, U_MCU.2
SEL_V3: R_S3.1, U_MCU.3
SEL_V4: R_S4.1, U_MCU.4
SW_V1: R_PD1.1, R_S1.2, U_SW.9
SW_V2: R_PD2.1, R_S2.2, U_SW.10
SW_V3: R_PD3.1, R_S3.2, U_SW.11
SW_V4: R_PD4.1, R_S4.2, U_SW.12

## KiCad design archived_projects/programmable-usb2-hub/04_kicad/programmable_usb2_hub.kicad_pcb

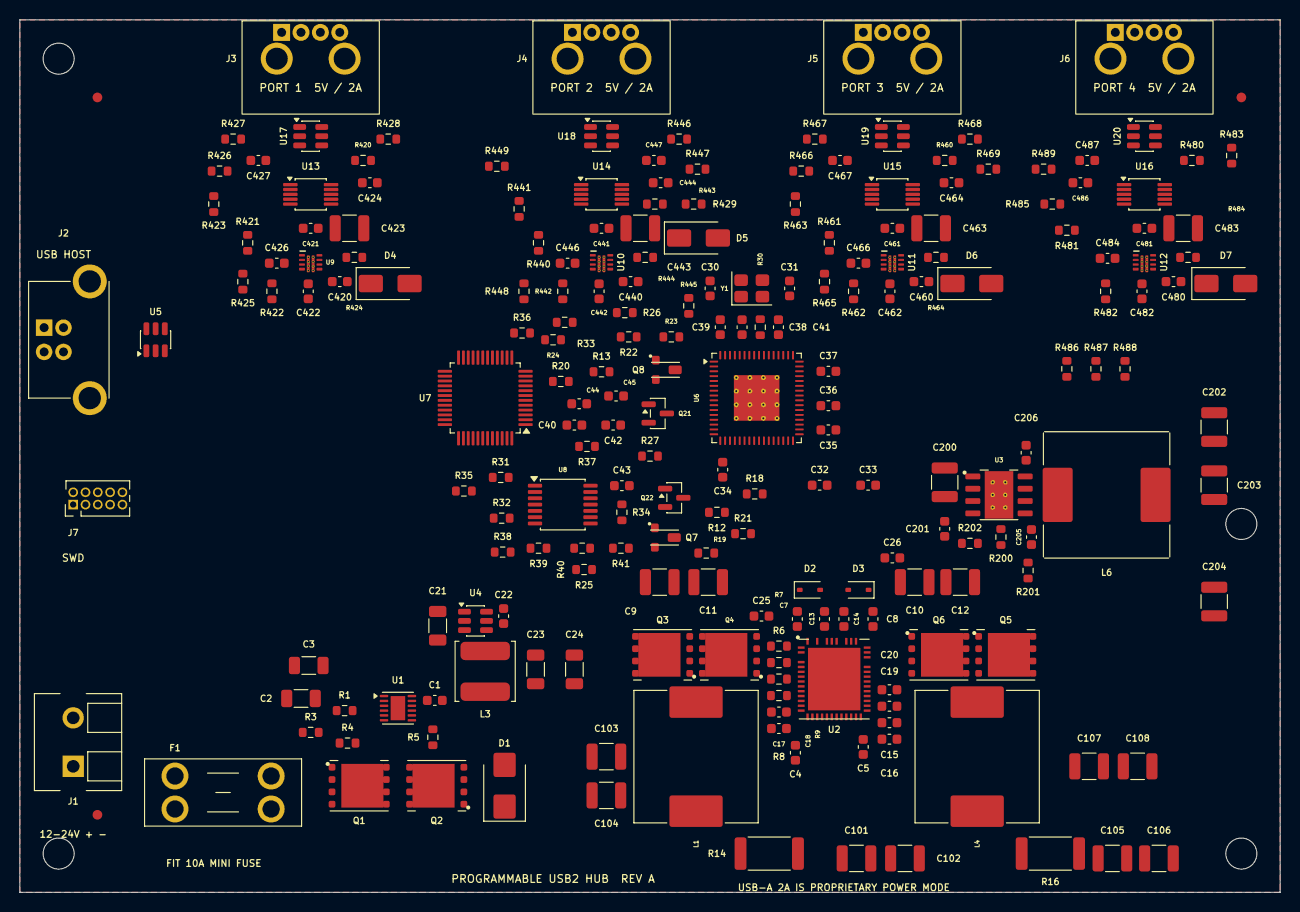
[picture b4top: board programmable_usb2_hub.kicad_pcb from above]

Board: 4 copper layers, 130.0 x 90.0 mm, 218 parts (0 on the bottom side), 151 nets, no tracks yet.

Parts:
C1, C201: 220nF; C_0603_1608Metric
C2, C3: 100nF; C_1206_3216Metric
C4, C5: 1nF; C_0603_1608Metric
C7, C8: 330nF; C_0603_1608Metric
C9, C10, C11, C12: 10uF; C_1210_3225Metric
C13, C14, C43: 4.7uF; C_0603_1608Metric
C15, C16, C36, C37, C40, C41, C205: 1uF; C_0603_1608Metric
C17, C19: 4.7nF; C_0603_1608Metric
C18, C20: 100pF; C_0603_1608Metric
C21: 10uF; C_1206_3216Metric
C22, C32, C33, C34, C35, C38, C39, C42, C44, C45, C206, C422, C424, C426, C427, C442, C444, C446, C447, C462, C464, C466, C467, C482, C484, C486, C487: 100nF; C_0603_1608Metric
C23, C24: 22uF; C_1206_3216Metric
C25, C26: 10nF; C_0603_1608Metric
C30, C31: 18pF; C_0603_1608Metric
C101, C102, C103, C104, C105, C106, C107, C108: 100uF; C_1210_3225Metric
C200: 2.2uF; C_1210_3225Metric
C202, C203, C204, C423, C443, C463, C483: 22uF; C_1210_3225Metric
C420, C440, C460, C480: 3.3nF; C_0603_1608Metric
C421, C441, C461, C481: 2.2nF; C_0603_1608Metric
D1: C224017; D_SMB
D2, D3: C2128; D_SOD-323
D4, D5, D6, D7: C85098; D_SMA
F1: 3568; Fuseholder_Blade_Mini_Keystone_3568
FID1, FID2, FID3: Fiducial_1mm_Mask2mm
H1, H2, H3, H4: MountingHole_3.2mm_M3
J1: C3819953; Phoenix_1935161_PT_1p5_2_5p0_H
J2: C86462; USB_B_TE_292304-1_Horizontal
J3, J4, J5, J6: USB1130-15-A; USB_A_GCT_USB1130_Horizontal
J7: C19191796; PinHeader_2x05_P1.27mm_Vertical
L1, L4: C408523; L_Sunlord_MWSA1206S-6R8
L3: C307880; L_TDK_VLS6045EX_VLS6045AF
L6: C2045462; TDK_B82477G4_12p8x12p8
Q1, Q2, Q3, Q4, Q5, Q6: CSD18533Q5AT; Texas_DQJ_Q5A_PhysicalPins
Q7, Q8: C85047; Diodes_SOT23_2N7002K
Q21, Q22: MMBT3906LT1G; SOT-23
R1, R4: 90.9kΩ; R_0603_1608Metric
R3: 4.64kΩ; R_0603_1608Metric
R5: 11.5kΩ; R_0603_1608Metric
R6, R7, R8, R9: 30Ω; R_0603_1608Metric
R12, R13, R18, R19, R24, R25, R26, R36, R37, R202, R422, R423, R429, R442, R443, R449, R462, R463, R469, R482, R483, R489: 10kΩ; R_0603_1608Metric
R14, R16: 10mΩ; R_2512_6332Metric
R20: 24.9kΩ; R_0603_1608Metric
R21: 9.09kΩ; R_0603_1608Metric
R22, R23, R32, R33, R38, R39, R40, R41, R200, R420, R426, R440, R446, R460, R466, R480, R486: 100kΩ; R_0603_1608Metric
R27: 5kΩ; R_0603_1608Metric
R30: 1MΩ; R_0603_1608Metric
R31: 12kΩ; R_0603_1608Metric
R34, R35: 4.7kΩ; R_0603_1608Metric
R201: 20kΩ; R_0603_1608Metric
R421, R441, R461, R481: 36.5kΩ; R_0603_1608Metric
R424, R444, R464, R484: 1.47kΩ; R_0603_1608Metric
R425, R428, R445, R448, R465, R468, R485, R488: 1kΩ; R_0603_1608Metric
R427, R447, R467, R487: 68kΩ; R_0603_1608Metric
U1: C3215601; WSON-12-1EP_3x3mm_P0.5mm_EP1.5x2.5mm
U2: LTC3889IUKG#PBF; Analog_UKG52_46_LTC3889
U3: C1858394; TI_DDA0008B_PowerPAD_SOIC-8
U4: C5248536; TSOT-23-6
U5, U17, U18, U19, U20: C7519; SOT-23-6
U6: C478081; QFN-64-1EP_9x9mm_P0.5mm_EP4.7x4.7mm_ThermalVias
U7: C2847904; LQFP-48_7x7mm_P0.5mm
U8: C6053; TSSOP-14_4.4x5mm_P0.65mm
U9, U10, U11, U12: C3662799; Texas_RPW0010A_VQFN-HR-10_2x2mm_P0.45mm_ThermalVias
U13, U14, U15, U16: C11355; MSOP-10_3x3mm_P0.5mm
Y1: C1985204; Crystal_SMD_3225-4Pin_3.2x2.5mm

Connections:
3V3_LOGIC: C23.1, C24.1, C32.1, C33.1, C34.1, C35.1, C36.1, C37.1, C38.1, C39.1, C42.1, C43.1, C44.1, C45.1, C427.1, C447.1, C467.1, C487.1, J7.1, L3.2, R12.1, R13.1, R18.1, R19.1, R22.1, R23.1, R24.1, R25.1, R26.1, R27.1, R34.1, R35.1, R37.2, R202.1, R423.1, R429.1, R443.1, R449.1, R463.1, R469.1, R483.1, R489.1, U4.1, U6.5, U6.10, U6.24, U6.35, U6.37, U6.38, U6.46, U6.52, U6.57, U6.64, U7.4, U7.5, U7.6, U8.14, U13.1, U14.1, U15.1, U16.1
5V_A: C101.1, C102.1, C103.1, C104.1, C422.1, C442.1, R7.1, R14.2, R421.1, R441.1, U2.7, U9.5, U10.5
5V_B: C105.1, C106.1, C107.1, C108.1, C462.1, C482.1, R9.1, R16.2, R461.1, R481.1, U2.35, U11.5, U12.5
ADC_P1_IMON: R425.2, U7.21
ADC_P1_VBUS: C426.1, R428.2, U7.11
ADC_P2_IMON: R445.2, U7.22
ADC_P2_VBUS: C446.1, R448.2, U7.12
ADC_P3_IMON: R465.2, U7.23
ADC_P3_VBUS: C466.1, R468.2, U7.19
ADC_P4_IMON: R485.2, U7.24
ADC_P4_VBUS: C486.1, R488.2, U7.20
AUX_6V: C14.1, C21.1, C202.1, C203.1, C204.1, L6.2, R200.1, U2.43, U4.2, U4.3
AUX_BOOT: C206.1, U3.7
AUX_FB: R200.2, R201.1, U3.5
AUX_PG_N: R202.2, U3.4
AUX_SW: C206.2, L6.1, U3.8
AUX_VCC: C205.1, U3.6
BG_A: Q4.4, U2.50
BG_B: Q6.4, U2.42
BOOST_A: C7.1, D2.1, U2.52
BOOST_B: C8.1, D3.1, U2.40
BST_3V3: C22.1, U4.6
CAP: C1.1, U1.11
DGATE: Q1.4, U1.1
DRVCC: C13.1, D2.2, D3.2, U2.44
FET_MID: C1.2, C2.1, Q1.5, Q1.6, Q1.7, Q1.8, Q1.9, Q2.5, Q2.6, Q2.7, Q2.8, Q2.9, U1.10, U1.12
FREQ_CFG: R20.2, R21.1, U2.25
GND: C2.2, C3.2, C9.2, C10.2, C11.2, C12.2, C13.2, C14.2, C15.2, C16.2, C17.2, C18.2, C19.2, C20.2, C21.2, C23.2, C24.2, C25.2, C26.2, C30.2, C31.2, C32.2, C33.2, C34.2, C35.2, C36.2, C37.2, C38.2, C39.2, C40.2, C41.2, C42.2, C43.2, C44.2, C45.2, C101.2, C102.2, C103.2, C104.2, C105.2, C106.2, C107.2, C108.2, C200.2, C201.2, C202.2, C203.2, C204.2, C205.2, C420.2, C421.2, C422.2, C423.2, C424.2, C426.2, C427.2, C440.2, C441.2, C442.2, C443.2, C444.2, C446.2, C447.2, C460.2, C461.2, C462.2, C463.2, C464.2, C466.2, C467.2, C480.2, C481.2, C482.2, C483.2, C484.2, C486.2, C487.2, D1.2, D4.2, D5.2, D6.2, D7.2, J1.2, J2.4, J2.5, J3.4, J3.5, J4.4, J4.5, J5.4, J5.5, J6.4, J6.5, J7.3, J7.5, J7.9, Q4.1, Q4.2, Q4.3, Q6.1, Q6.2, Q6.3, Q7.2, Q8.2, Q21.1, Q21.3, Q22.1, Q22.3, R3.2, R5.2, R21.2, R31.2, R33.2, R36.2, R38.2, R39.2, R40.2, R41.2, R201.2, R420.2, R422.2, R424.2, R427.2, R440.2, R442.2, R444.2, R447.2, R460.2, R462.2, R464.2, R467.2, R480.2, R482.2, R484.2, R487.2, U1.7, U2.8, U2.26, U2.28, U2.53, U3.1, U3.9, U4.4, U5.2, U6.13, U6.42, U6.65, U7.7, U8.7, U9.8, U10.8, U11.8, U12.8, U13.2, U13.5, U14.2, U14.5, U15.2, U15.5, U16.2, U16.5, U17.2, U18.2, U19.2, U20.2, Y1.2, Y1.4
HGATE: Q2.4, U1.8
HUB_PP1: U6.29, U8.1
HUB_PP2: U6.26, U8.4
HUB_PP3: U6.23, U8.9
HUB_PP4: U6.20, U8.12
HUB_RESET_N: R36.1, U6.43, U7.42
HUB_SCL: R35.2, U2.14, U6.41, U7.40
HUB_SDA: R34.2, U2.15, U6.40, U7.41
HUB_VBUS_DET: R32.2, R33.1, U6.44
ISNS_A_NF: C4.2, R7.2, U2.5
ISNS_A_PF: C4.1, R6.2, U2.4
ISNS_B_NF: C5.2, R9.2, U2.10
ISNS_B_PF: C5.1, R8.2, U2.9
ITHR_A: C18.1, U2.11
ITHR_B: C20.1, U2.32
ITH_A: C17.1, U2.12
ITH_B: C19.1, U2.31
LTC_ALERT_N: R12.2, U2.16
LTC_FAULT_N: R13.2, U2.17, U2.18
LTC_SYNC: R27.2, U2.13
LTC_VDD33: C16.1, U2.30
MCU_NRST: J7.10, R37.1, U7.10
MGMT_N: U6.11, U7.33
MGMT_P: U6.12, U7.34
OV_SENSE: R1.2, R3.1, U1.5
OV_TOP: R1.1, U1.4
P1_CONN_N: J3.2, U17.4
P1_CONN_P: J3.3, U17.6
P1_DATA_ISO: R429.2, U7.17, U13.10
P1_DVDT: C420.1, U9.7
P1_FLT_N: R423.2, U6.28, U7.27, U9.4
P1_HUB_N: U6.1, U13.4
P1_HUB_P: U6.2, U13.3
P1_ILIM: R424.1, R425.1, U9.9
P1_ITIMER: C421.1, U9.10
P1_OVLO: R421.2, R422.1, U9.2
P1_PORT_N: U13.6, U17.3
P1_PORT_P: U13.7, U17.1
P1_PWR_CMD: R38.1, U7.13, U8.2
P1_PWR_EN: R420.1, U8.3, U9.1
P1_VBUS: C423.1, C424.1, D4.1, J3.1, R426.1, U9.6, U17.5
P1_VBUS_SENSE: R426.2, R427.1, R428.1
P2_CONN_N: J4.2, U18.4
P2_CONN_P: J4.3, U18.6
P2_DATA_ISO: R449.2, U7.18, U14.10
P2_DVDT: C440.1, U10.7
P2_FLT_N: R443.2, U6.27, U7.28, U10.4
P2_HUB_N: U6.3, U14.4
P2_HUB_P: U6.4, U14.3
P2_ILIM: R444.1, R445.1, U10.9
P2_ITIMER: C441.1, U10.10
P2_OVLO: R441.2, R442.1, U10.2
P2_PORT_N: U14.6, U18.3
P2_PORT_P: U14.7, U18.1
P2_PWR_CMD: R39.1, U7.14, U8.5
P2_PWR_EN: R440.1, U8.6, U10.1
P2_VBUS: C443.1, C444.1, D5.1, J4.1, R446.1, U10.6, U18.5
P2_VBUS_SENSE: R446.2, R447.1, R448.1
P3_CONN_N: J5.2, U19.4
P3_CONN_P: J5.3, U19.6
P3_DATA_ISO: R469.2, U7.25, U15.10
P3_DVDT: C460.1, U11.7
P3_FLT_N: R463.2, U6.22, U7.29, U11.4
P3_HUB_N: U6.6, U15.4
P3_HUB_P: U6.7, U15.3
P3_ILIM: R464.1, R465.1, U11.9
P3_ITIMER: C461.1, U11.10
P3_OVLO: R461.2, R462.1, U11.2
P3_PORT_N: U15.6, U19.3
P3_PORT_P: U15.7, U19.1
P3_PWR_CMD: R40.1, U7.15, U8.10
P3_PWR_EN: R460.1, U8.8, U11.1
P3_VBUS: C463.1, C464.1, D6.1, J5.1, R466.1, U11.6, U19.5
P3_VBUS_SENSE: R466.2, R467.1, R468.1
P4_CONN_N: J6.2, U20.4
P4_CONN_P: J6.3, U20.6
P4_DATA_ISO: R489.2, U7.26, U16.10
P4_DVDT: C480.1, U12.7
P4_FLT_N: R483.2, U6.21, U7.30, U12.4
P4_HUB_N: U6.8, U16.4
P4_HUB_P: U6.9, U16.3
P4_ILIM: R484.1, R485.1, U12.9
P4_ITIMER: C481.1, U12.10
P4_OVLO: R481.2, R482.1, U12.2
P4_PORT_N: U16.6, U20.3
P4_PORT_P: U16.7, U20.1
P4_PWR_CMD: R41.1, U7.16, U8.13
P4_PWR_EN: R480.1, U8.11, U12.1
P4_VBUS: C483.1, C484.1, D7.1, J6.1, R486.1, U12.6, U20.5
P4_VBUS_SENSE: R486.2, R487.1, R488.1
PGOOD_A_N: R25.2, U2.34
PGOOD_B_N: R26.2, U2.33
RBIAS: R31.1, U6.63
RUN_A: Q7.3, R18.2, U2.19
RUN_A_HOLD: Q7.1, R22.2, U7.31
RUN_B: Q8.3, R19.2, U2.20
RUN_B_HOLD: Q8.1, R23.2, U7.32
SENSE_A: L1.2, R6.1, R14.1
SENSE_B: L4.2, R8.1, R16.1
SHARE_CLK: R24.2, U2.29
SWCLK: J7.4, U7.36
SWDIO: J7.2, U7.35
SW_3V3: C22.2, L3.1, U4.5
SW_A: C7.2, L1.1, Q3.1, Q3.2, Q3.3, Q4.5, Q4.6, Q4.7, Q4.8, Q4.9, U2.1
SW_B: C8.2, L4.1, Q5.1, Q5.2, Q5.3, Q6.5, Q6.6, Q6.7, Q6.8, Q6.9, U2.39
TG_A: Q3.4, U2.2
TG_B: Q5.4, U2.38
TSNS_A: C25.1, Q21.2, U2.6
TSNS_B: C26.1, Q22.2, U2.36
UP_CONN_N: J2.2, U5.3
UP_CONN_P: J2.3, U5.1
UP_HUB_N: U5.4, U6.58
UP_HUB_P: U5.6, U6.59
USB_UP_VBUS: J2.1, R32.1, U5.5
UV_SENSE: R4.2, R5.1, U1.6
VDD18: C40.1, U6.25
VDD18PLL: C41.1, U6.62
VDD25: C15.1, R20.1, U2.27
VIN_FUSED: C3.1, F1.2, Q1.1, Q1.2, Q1.3, R4.1, U1.2, U1.3
VIN_PROTECTED: C9.1, C10.1, C11.1, C12.1, C200.1, C201.1, D1.1, Q2.1, Q2.2, Q2.3, Q3.5, Q3.6, Q3.7, Q3.8, Q3.9, Q5.5, Q5.6, Q5.7, Q5.8, Q5.9, U1.9, U2.46, U2.47, U2.48, U3.2, U3.3
VIN_RAW: F1.1, J1.1
XTAL1: C30.1, R30.1, U6.61, Y1.1
XTAL2: C31.1, R30.2, U6.60, Y1.3
